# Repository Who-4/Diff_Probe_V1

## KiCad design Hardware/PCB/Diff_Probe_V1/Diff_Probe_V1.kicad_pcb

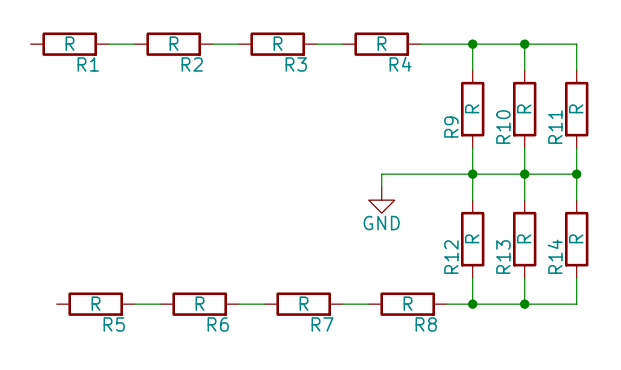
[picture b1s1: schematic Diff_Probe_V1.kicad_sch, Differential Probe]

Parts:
R1, R2, R3, R4, R5, R6, R7, R8, R9, R10, R11, R12, R13, R14: R; R_0805_2012Metric

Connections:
GND: R9.2, R10.2, R11.2, R12.1, R13.1, R14.1
unnamed: R1.2, R2.1
unnamed: R2.2, R3.1
unnamed: R3.2, R4.1
unnamed: R5.2, R6.1
unnamed: R6.2, R7.1
unnamed: R7.2, R8.1
unnamed: R4.2, R9.1, R10.1, R11.1
unnamed: R8.2, R12.2, R13.2, R14.2

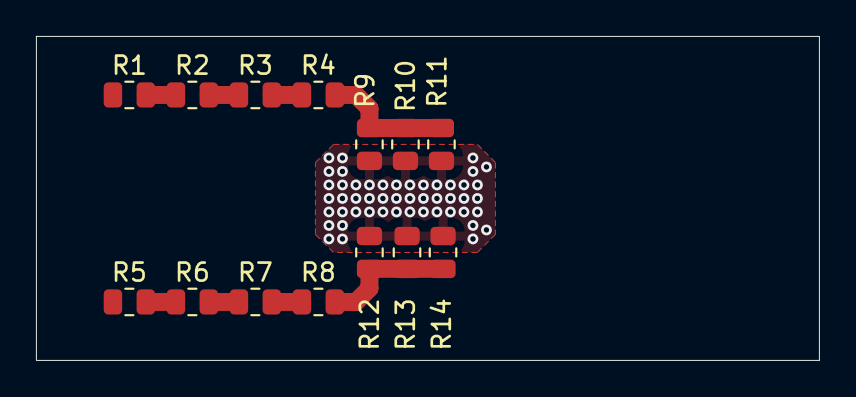
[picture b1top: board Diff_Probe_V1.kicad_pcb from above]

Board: 2 copper layers, 43.5 x 18.0 mm, 14 parts (0 on the bottom side), 9 nets.
